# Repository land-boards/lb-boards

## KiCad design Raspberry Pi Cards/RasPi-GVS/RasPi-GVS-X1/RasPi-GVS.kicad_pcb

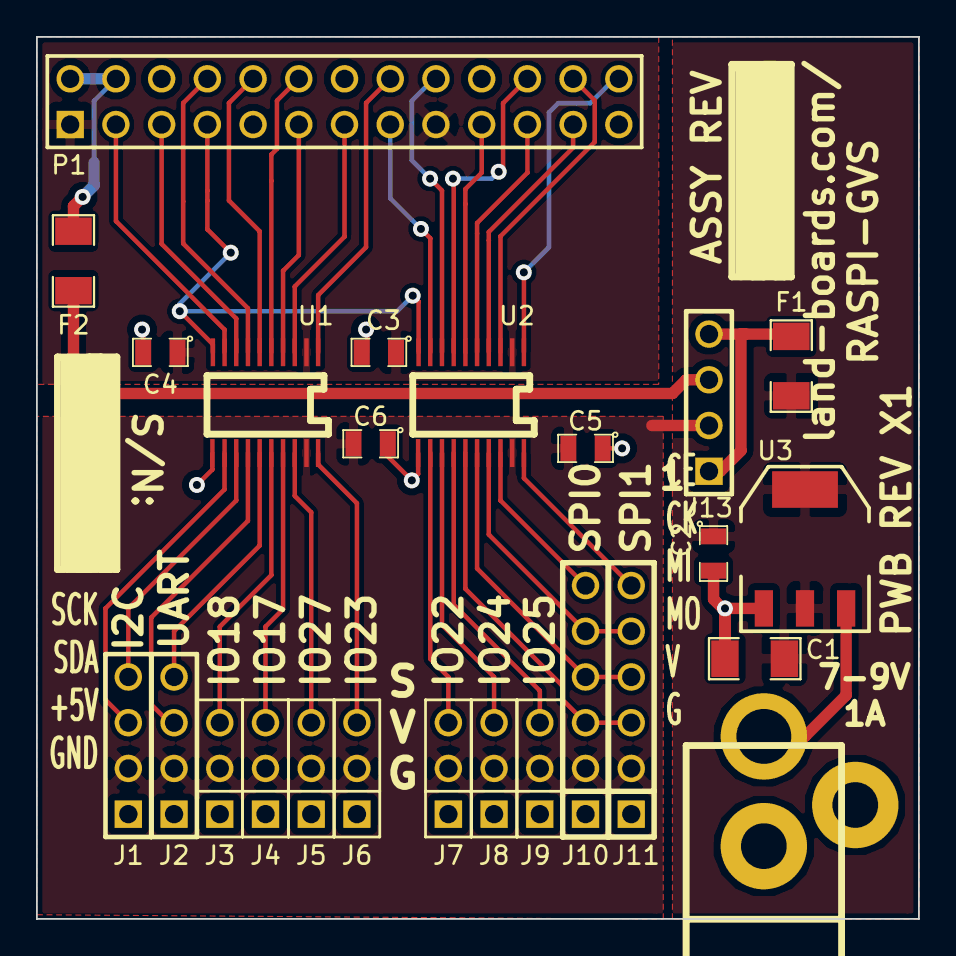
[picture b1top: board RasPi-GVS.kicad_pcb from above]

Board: 2 copper layers, 49.0 x 49.0 mm, 27 parts (0 on the bottom side), 41 nets.

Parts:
C1: 106; SM1206
C2, C3, C4, C5, C6: 104; SM0805
COUP?1, COUP?2: COUPON; REV_BLOCK
F1, F2: FUSE; SM1206
J1, J2, J13: CONN_4; PIN_ARRAY_4x1
J3, J4, J5, J6, J7, J8, J9: CONN_3; PIN_ARRAY_3X1
J10, J11: CONN_6; PIN_ARRAY-6X1
J12: JACK-3.5MM; JACK_2.1MM
P1: RASPIO; pin_array_13x2
U1, U2: TXB0108; SOG20
U3: AP1117; SOT223

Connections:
/+3.3V: C3.1, C4.1, P1.1, P1.17, U1.2, U2.2
/BIO_17: J4.3, U1.17
/BIO_18: J3.3, U1.16
/BIO_22: J7.3, U2.12
/BIO_23: J6.3, U1.20
/BIO_24: J8.3, U2.13
/BIO_25: J9.3, U2.14
/BIO_27: J5.3, U1.18
/BRXD0: J2.4, U1.15
/BSCLK1: J1.4, U1.13
/BSDA1: J1.3, U1.12
/BSPICE0: J10.6, U2.18
/BSPICE1: J11.6, U2.20
/BSPIMISO: J10.4, J11.4, U2.16
/BSPIMOSI: J10.3, J11.3, U2.15
/BSPISCK: J10.5, J11.5, U2.17
/BTXD0: J2.3, U1.14
/GND: C1.2, C2.2, C3.2, C4.2, C5.1, C6.1, J1.1, J2.1, J3.1, J4.1, J5.1, J6.1, J7.1, J8.1, J9.1, J10.1, J11.1, J12.2, J12.3, P1.6, P1.9, P1.14, P1.20, P1.25, U1.11, U2.11, U3.1
/GV5V: C5.2, C6.2, J1.2, J2.2, J3.2, J4.2, J5.2, J6.2, J7.2, J8.2, J9.2, J10.2, J11.2, J13.2, U1.19, U2.19
/IO_4: P1.7, U1.10, U2.10
/IO_17: P1.11, U1.4
/IO_18: P1.12, U1.5
/IO_22: P1.15, U2.9
/IO_23: P1.16, U1.1
/IO_24: P1.18, U2.8
/IO_25: P1.22, U2.7
/IO_27: P1.13, U1.3
/R5: F2.1, P1.2, P1.4
/RP5V: F2.2, J13.3
/RXD0: P1.10, U1.6
/SCLK1: P1.5, U1.8
/SDA1: P1.3, U1.9
/SPICE0: P1.24, U2.3
/SPICE1: P1.26, U2.1
/SPIMISO: P1.21, U2.5
/SPIMOSI: P1.19, U2.6
/SPISCK: P1.23, U2.4
/TXD0: P1.8, U1.7
/VR5V: F1.2, J13.1, J13.4
/VRIN: J12.1, U3.3
/VROUT: C1.1, C2.1, F1.1, U3.2, U3.4

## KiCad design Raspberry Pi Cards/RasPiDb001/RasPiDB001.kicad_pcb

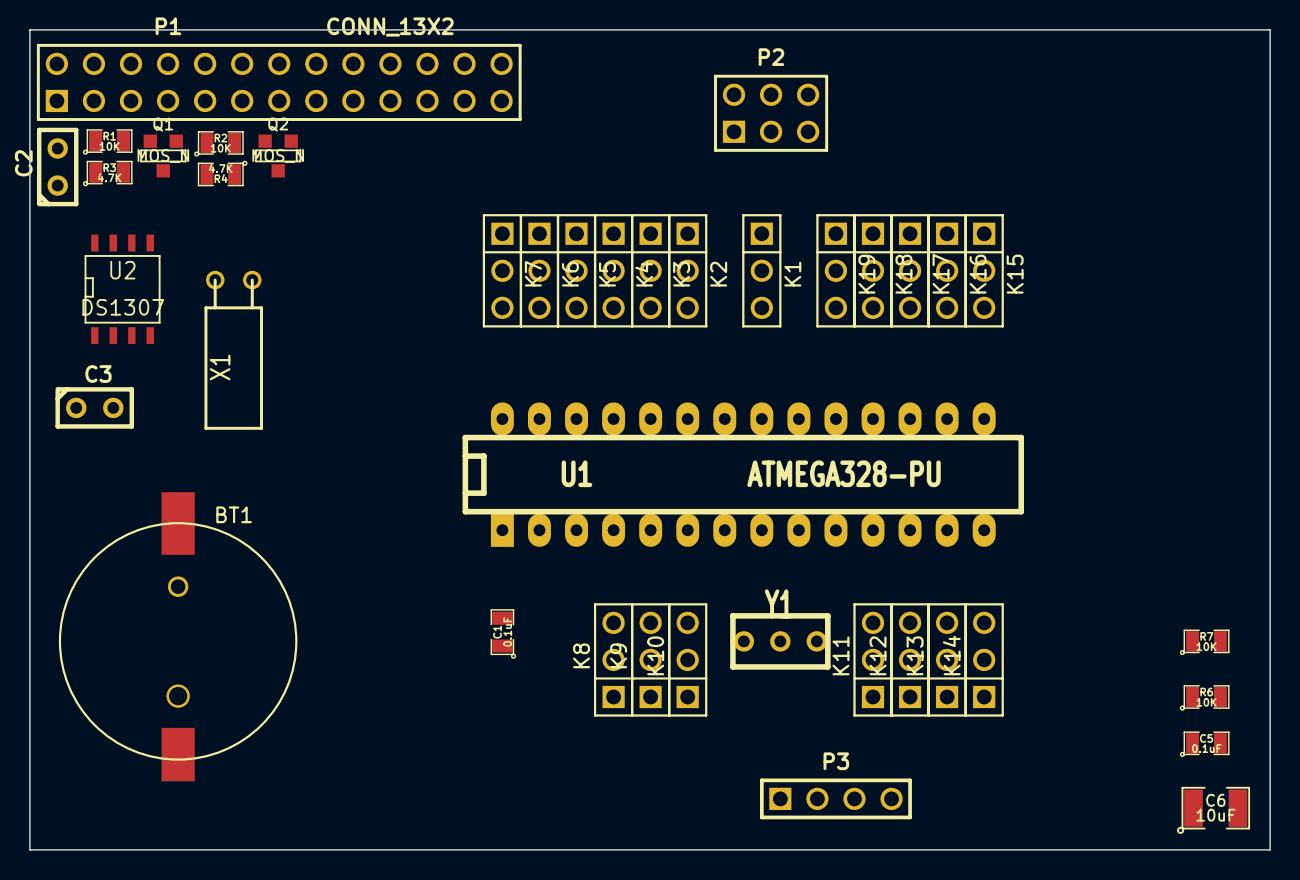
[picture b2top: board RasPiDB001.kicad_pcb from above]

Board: 2 copper layers, 85.0 x 56.2 mm, 40 parts (0 on the bottom side), 35 nets, no tracks yet.

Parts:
BT1: BATTERY; CR1220_CASE
C1, C5: 0.1uF; SM0805
C2, C3: 0.1uF; C1
C6: 10uF; SM1210
K1, K2, K3, K4, K5, K6, K7, K8, K9, K10, K11, K12, K13, K14, K15, K16, K17, K18, K19: CONN_3; PIN_ARRAY_3X1
P1: CONN_13X2; pin_array_13x2
P2: CONN_3X2; pin_array_3x2
P3: CONN_4; PIN_ARRAY_4x1
Q1, Q2: MOS_N; SOT23GDS
R1, R2, R6, R7: 10K; SM0805
R3, R4: 4.7K; SM0805
U1: ATMEGA328-PU; DIP-28__300_ELL
U2: DS1307; SO8N
X1: 32.768KHz; QMONTRE
Y1: 16MHz; RESON_3PIN

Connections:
+3.3V: P1.1, Q1.G, Q2.G, R1.1, R2.1
+5V: C1.1, C3.1, C5.1, C6.1, K1.1, K8.2, K9.2, K10.2, K11.2, K12.2, K13.2, K14.2, K15.2, K16.2, K17.2, K18.2, K19.2, P1.2, P2.2, P3.2, R3.1, R4.2, R6.1, R7.1, U1.7, U1.20, U2.8
/Microprocessor/AD0: K2.3, U1.23
/Microprocessor/AD1: K3.3, U1.24
/Microprocessor/AD2: K4.3, U1.25
/Microprocessor/AD3: K5.3, U1.26
/Microprocessor/AD4: K6.3, U1.27
/Microprocessor/AD5: K7.3, U1.28
/Microprocessor/ARDRX: Q1.D, R3.2, U1.2
/Microprocessor/ARDTX: Q2.D, R4.1, U1.3
/Microprocessor/AREF: K1.3, U1.21
/Microprocessor/D2: K8.3, U1.4
/Microprocessor/D3: K9.3, U1.5
/Microprocessor/D4: K10.3, U1.6
/Microprocessor/D5: K11.3, U1.11
/Microprocessor/D6: K12.3, U1.12
/Microprocessor/D7: K13.3, U1.13
/Microprocessor/D8: K14.3, U1.14
/Microprocessor/D9: K15.3, U1.15
/Microprocessor/D10: K16.3, U1.16
/Microprocessor/D11: K17.3, U1.17
/Microprocessor/D12: K18.3, U1.18
/Microprocessor/D13: K19.3, U1.19
/Microprocessor/RES0: U1.9, Y1.1
/Microprocessor/RES1: U1.10, Y1.3
/RTC/SCLK: P3.4, R6.2, U2.6
/RTC/SDA: P3.3, R7.2, U2.5
/TxRx Transl/PIRX: P1.10, Q2.S, R2.2
/TxRx Transl/PITX: P1.8, Q1.S, R1.2
GND: BT1.2, C1.2, C3.2, C5.2, C6.2, K2.1, K3.1, K4.1, K5.1, K6.1, K7.1, K8.1, K9.1, K10.1, K11.1, K12.1, K13.1, K14.1, K15.1, K16.1, K17.1, K18.1, K19.1, P2.6, P3.1, U1.8, U1.22, U2.4, Y1.2
unnamed: C2.2, U1.1
unnamed: K1.2, K2.2, K3.2, K4.2, K5.2, K6.2, K7.2
unnamed: BT1.1, U2.3
unnamed: U2.1, X1.1
unnamed: U2.2, X1.2

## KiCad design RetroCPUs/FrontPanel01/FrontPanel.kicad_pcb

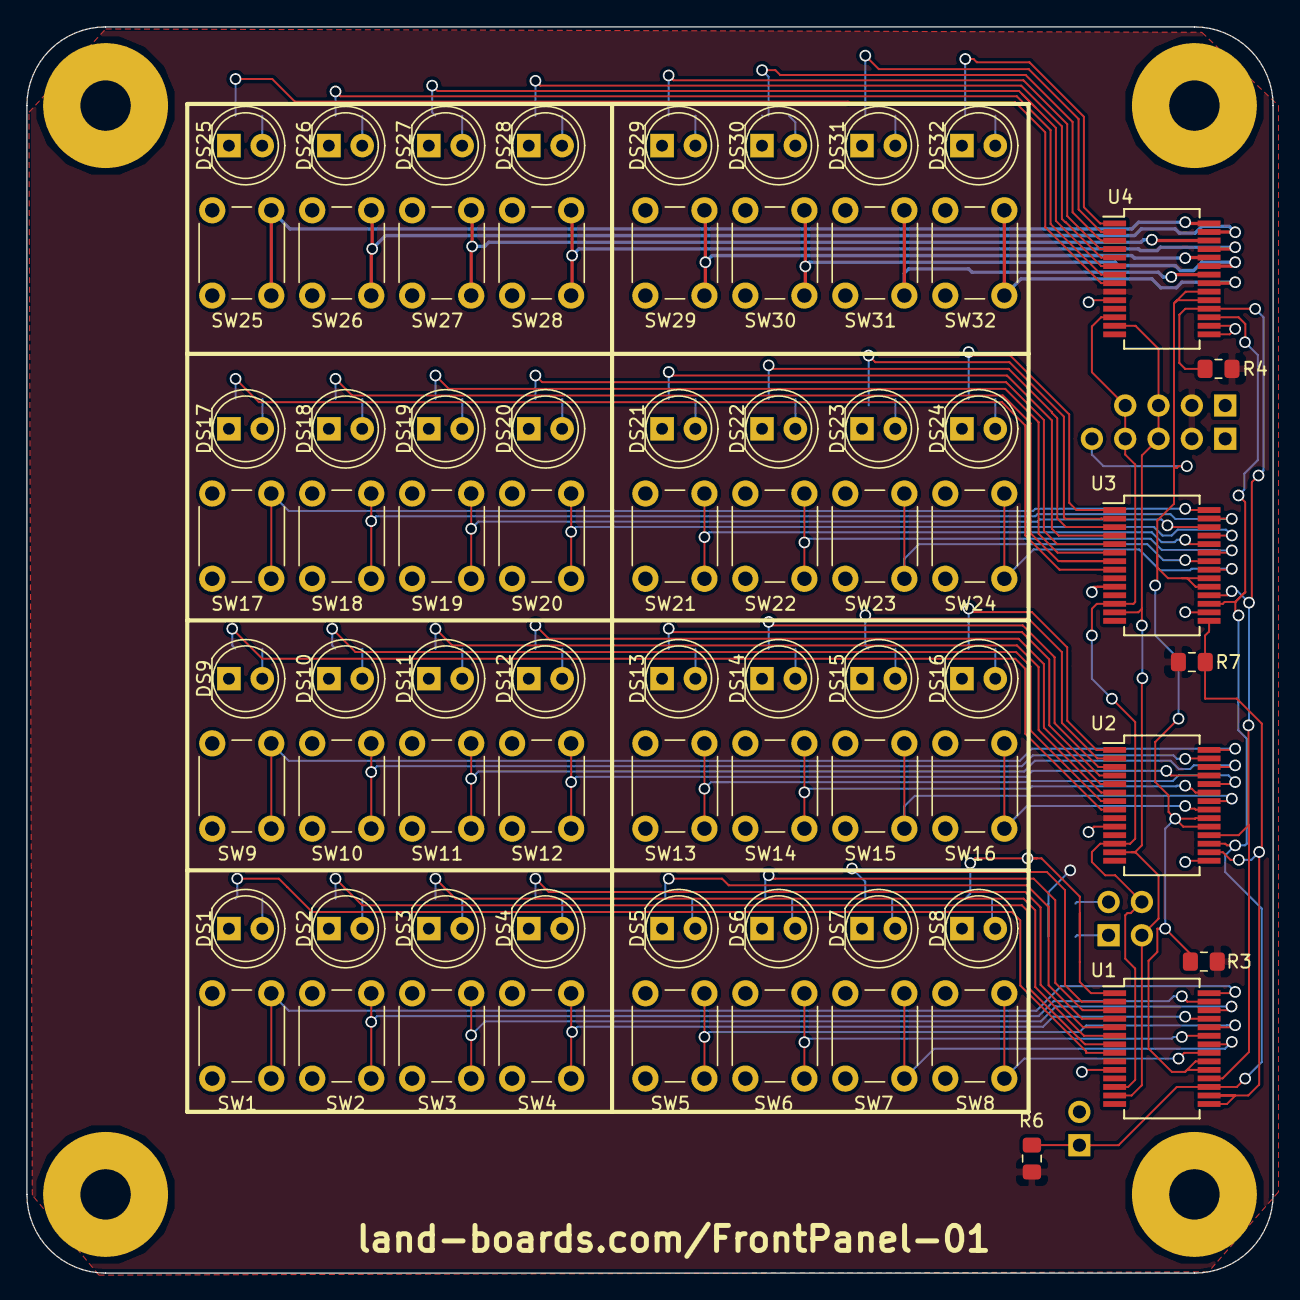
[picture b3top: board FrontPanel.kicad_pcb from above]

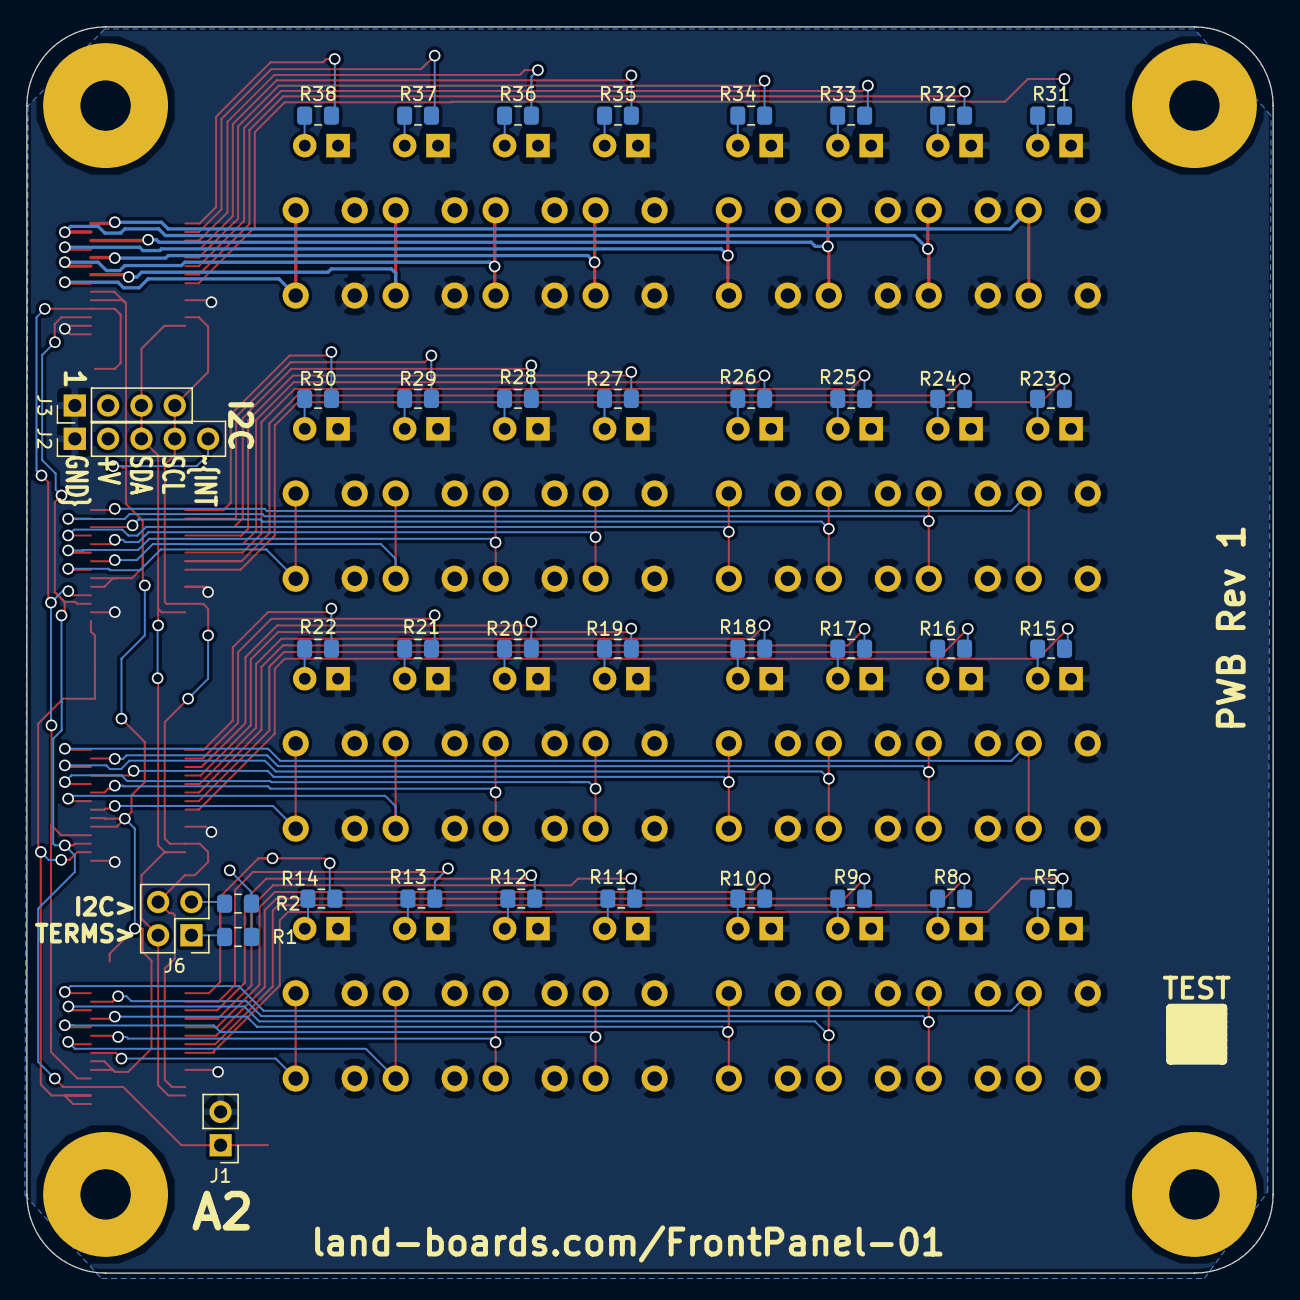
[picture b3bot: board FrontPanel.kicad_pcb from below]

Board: 2 copper layers, 95.0 x 95.0 mm, 115 parts (38 on the bottom side), 106 nets.

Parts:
DS1, DS2, DS3, DS4, DS5, DS6, DS7, DS8, DS9, DS10, DS11, DS12, DS13, DS14, DS15, DS16, DS17, DS18, DS19, DS20, DS21, DS22, DS23, DS24, DS25, DS26, DS27, DS28, DS29, DS30, DS31, DS32: LED; LED_D5.0mm
J1: Conn_01x02; PinHeader_1x02_P2.54mm_Vertical
J2: Conn_01x05; PinHeader_1x05_P2.54mm_Vertical
J3: CONN_4; PinHeader_1x04_P2.54mm_Vertical
J6: CONN_02X02; PinHeader_2x02_P2.54mm_Vertical
MTG1, MTG2, MTG3, MTG4: MTG_HOLE; MTG-6-32
R1, R2: 2.2K; R_0805_2012Metric_Pad1.15x1.40mm_HandSolder
R3, R4, R6, R7: 10K; R_0805_2012Metric_Pad1.15x1.40mm_HandSolder
R5, R8, R9, R10, R11, R12, R13, R14, R15, R16, R17, R18, R19, R20, R21, R22, R23, R24, R25, R26, R27, R28, R29, R30, R31, R32, R33, R34, R35, R36, R37, R38: 330; R_0805_2012Metric_Pad1.15x1.40mm_HandSolder
SW1, SW2, SW3, SW4, SW5, SW6, SW7, SW8, SW9, SW10, SW11, SW12, SW13, SW14, SW15, SW16, SW17, SW18, SW19, SW20, SW21, SW22, SW23, SW24, SW25, SW26, SW27, SW28, SW29, SW30, SW31, SW32: SW_Push; SW_PUSH_6mm
TEST: CONN_1; TEST_BLK-REAR
U1, U2, U3, U4: MCP23017-E/SS; SSOP-28_5.3x10.2mm_P0.65mm

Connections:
+5V: J2.2, J3.2, R1.2, R2.2, R3.1, R4.1, R6.2, R7.1, U1.9, U2.9, U3.9, U4.9
/A2: J1.1, R6.1, U1.17, U2.17, U3.17, U4.17
/PUPADR: R7.2, U1.15, U1.16, U2.16, U3.15
/PUPINT: J2.5, R3.2, U1.19, U1.20, U2.19, U2.20, U3.19, U3.20, U4.19, U4.20
/PUPRST: R4.2, U1.18, U2.18, U3.18, U4.18
/S1D0: SW8.2, U1.21
/S1D1: SW7.2, U1.22
/S1D2: SW6.2, U1.23
/S1D3: SW5.2, U1.24
/S1D4: SW4.2, U1.25
/S1D5: SW3.2, U1.26
/S1D6: SW2.2, U1.27
/S1D7: SW1.2, U1.28
/S2D0: SW16.2, U2.21
/S2D1: SW15.2, U2.22
/S2D2: SW14.2, U2.23
/S2D3: SW13.2, U2.24
/S2D4: SW12.2, U2.25
/S2D5: SW11.2, U2.26
/S2D6: SW10.2, U2.27
/S2D7: SW9.2, U2.28
/S3D0: SW24.2, U3.21
/S3D1: SW23.2, U3.22
/S3D2: SW22.2, U3.23
/S3D3: SW21.2, U3.24
/S3D4: SW20.2, U3.25
/S3D5: SW19.2, U3.26
/S3D6: SW18.2, U3.27
/S3D7: SW17.2, U3.28
/S4D0: SW32.2, U4.21
/S4D1: SW31.2, U4.22
/S4D2: SW30.2, U4.23
/S4D3: SW29.2, U4.24
/S4D4: SW28.2, U4.25
/S4D5: SW27.2, U4.26
/S4D6: SW26.2, U4.27
/S4D7: SW25.2, U4.28
/SCL: J2.4, J3.4, J6.4, U1.12, U2.12, U3.12, U4.12
/SDA: J2.3, J3.3, J6.2, U1.13, U2.13, U3.13, U4.13
GND: DS1.1, DS2.1, DS3.1, DS4.1, DS5.1, DS6.1, DS7.1, DS8.1, DS9.1, DS10.1, DS11.1, DS12.1, DS13.1, DS14.1, DS15.1, DS16.1, DS17.1, DS18.1, DS19.1, DS20.1, DS21.1, DS22.1, DS23.1, DS24.1, DS25.1, DS26.1, DS27.1, DS28.1, DS29.1, DS30.1, DS31.1, DS32.1, J1.2, J2.1, J3.1, SW1.1, SW2.1, SW3.1, SW4.1, SW5.1, SW6.1, SW7.1, SW8.1, SW9.1, SW10.1, SW11.1, SW12.1, SW13.1, SW14.1, SW15.1, SW16.1, SW17.1, SW18.1, SW19.1, SW20.1, SW21.1, SW22.1, SW23.1, SW24.1, SW25.1, SW26.1, SW27.1, SW28.1, SW29.1, SW30.1, SW31.1, SW32.1, U1.10, U2.10, U2.15, U3.10, U3.16, U4.10, U4.15, U4.16
unnamed: DS1.2, R5.1
unnamed: DS2.2, R8.1
unnamed: DS3.2, R9.1
unnamed: DS4.2, R10.1
unnamed: DS5.2, R11.1
unnamed: DS6.2, R12.1
unnamed: DS7.2, R13.1
unnamed: DS8.2, R14.1
unnamed: DS9.2, R15.1
unnamed: DS10.2, R16.1
unnamed: DS11.2, R17.1
unnamed: DS12.2, R18.1
unnamed: DS13.2, R19.1
unnamed: DS14.2, R20.1
unnamed: DS15.2, R21.1
unnamed: DS16.2, R22.1
unnamed: DS17.2, R23.1
unnamed: DS18.2, R24.1
unnamed: DS19.2, R25.1
unnamed: DS20.2, R26.1
unnamed: DS21.2, R27.1
unnamed: DS22.2, R28.1
unnamed: DS23.2, R29.1
unnamed: DS24.2, R30.1
unnamed: DS25.2, R31.1
unnamed: DS26.2, R32.1
unnamed: DS27.2, R33.1
unnamed: DS28.2, R34.1
unnamed: DS29.2, R35.1
unnamed: DS30.2, R36.1
unnamed: DS31.2, R37.1
unnamed: DS32.2, R38.1
unnamed: J6.1, R1.1
unnamed: J6.3, R2.1
unnamed: R5.2, U1.8
unnamed: R8.2, U1.7
unnamed: R9.2, U1.6
unnamed: R10.2, U1.5
unnamed: R11.2, U1.4
unnamed: R12.2, U1.3
unnamed: R13.2, U1.2
unnamed: R14.2, U1.1
unnamed: R15.2, U2.8
unnamed: R16.2, U2.7
unnamed: R17.2, U2.6
unnamed: R18.2, U2.5
unnamed: R19.2, U2.4
unnamed: R20.2, U2.3
unnamed: R21.2, U2.2
unnamed: R22.2, U2.1
unnamed: R23.2, U3.8
unnamed: R24.2, U3.7
unnamed: R25.2, U3.6
unnamed: R26.2, U3.5
unnamed: R27.2, U3.4
unnamed: R28.2, U3.3
unnamed: R29.2, U3.2
unnamed: R30.2, U3.1
unnamed: R31.2, U4.8
unnamed: R32.2, U4.7
unnamed: R33.2, U4.6
unnamed: R34.2, U4.5
unnamed: R35.2, U4.4
unnamed: R36.2, U4.3
unnamed: R37.2, U4.2
unnamed: R38.2, U4.1

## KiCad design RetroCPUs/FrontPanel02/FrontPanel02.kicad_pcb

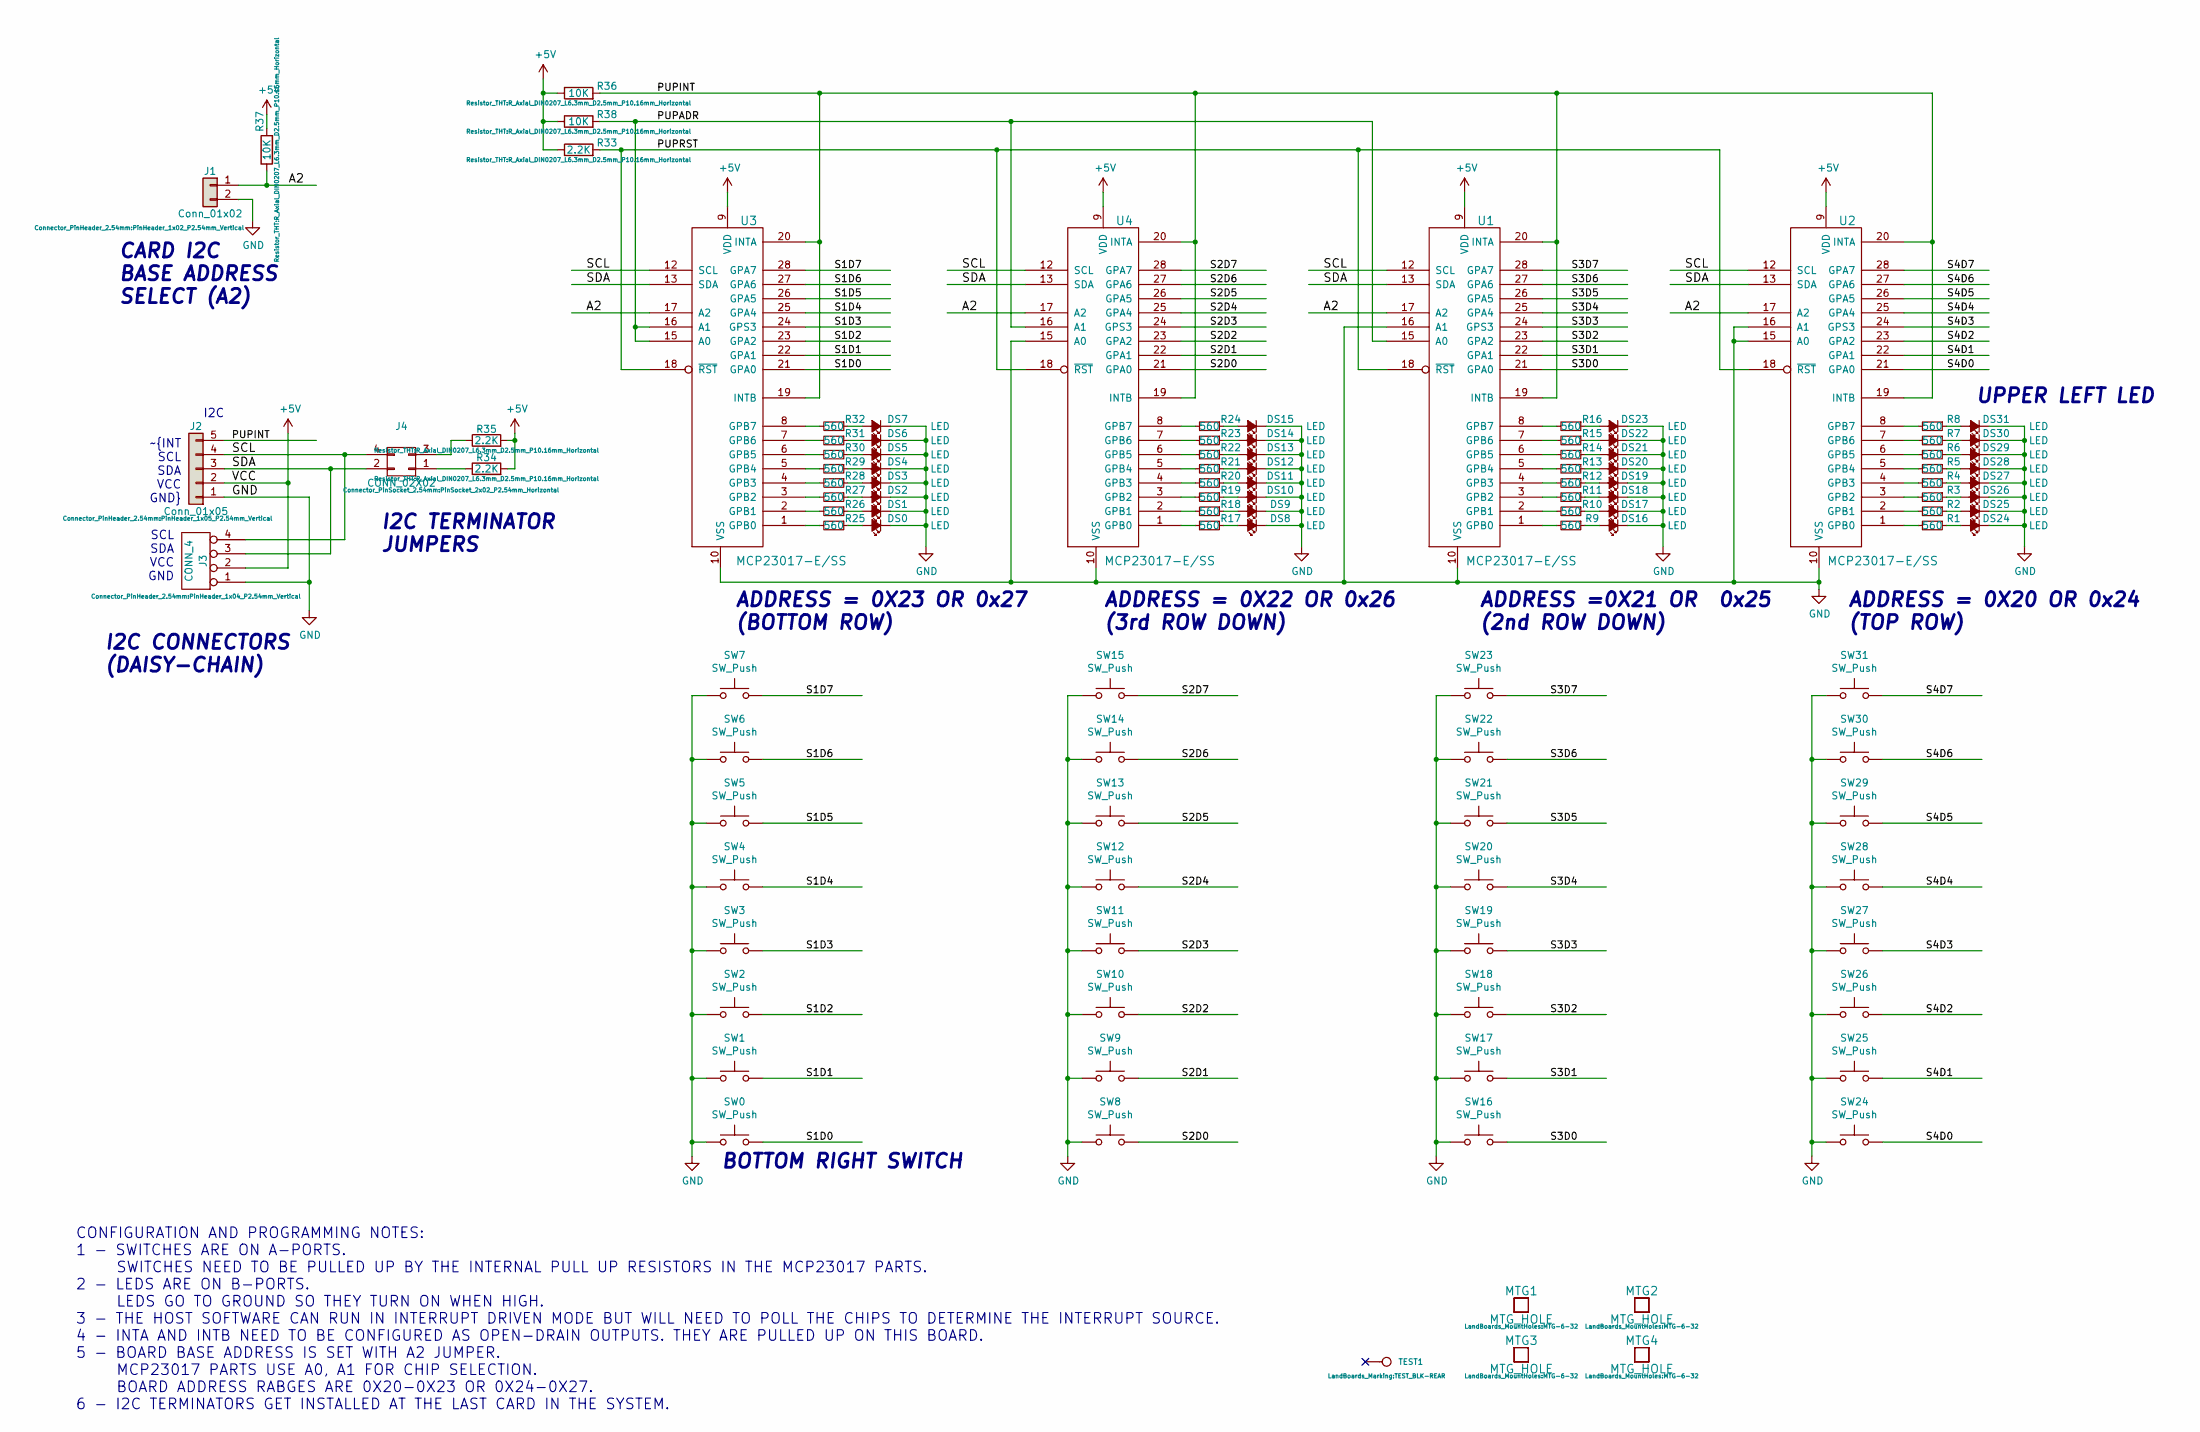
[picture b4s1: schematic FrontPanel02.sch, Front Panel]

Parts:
DS0, DS1, DS2, DS3, DS4, DS5, DS6, DS7, DS8, DS9, DS10, DS11, DS12, DS13, DS14, DS15, DS16, DS17, DS18, DS19, DS20, DS21, DS22, DS23, DS24, DS25, DS26, DS27, DS28, DS29, DS30, DS31: LED; LED_D5.0mm
J1: Conn_01x02; PinHeader_1x02_P2.54mm_Vertical
J2: Conn_01x05; PinHeader_1x05_P2.54mm_Vertical
J3: CONN_4; PinHeader_1x04_P2.54mm_Vertical
J4: CONN_02X02; PinSocket_2x02_P2.54mm_Horizontal
MTG1, MTG2, MTG3, MTG4: MTG_HOLE; MTG-6-32
R1, R2, R3, R4, R5, R6, R7, R8, R9, R10, R11, R12, R13, R14, R15, R16, R17, R18, R19, R20, R21, R22, R23, R24, R25, R26, R27, R28, R29, R30, R31, R32: 560; R_Axial_DIN0207_L6.3mm_D2.5mm_P10.16mm_Horizontal
R33, R34, R35: 2.2K; R_Axial_DIN0207_L6.3mm_D2.5mm_P10.16mm_Horizontal
R36, R37, R38: 10K; R_Axial_DIN0207_L6.3mm_D2.5mm_P10.16mm_Horizontal
SW0, SW1, SW2, SW3, SW4, SW5, SW6, SW7, SW8, SW9, SW10, SW11, SW12, SW13, SW14, SW15, SW16, SW17, SW18, SW19, SW20, SW21, SW22, SW23, SW24, SW25, SW26, SW27, SW28, SW29, SW30, SW31: SW_Push; SW_PUSH_6mm
TEST1: CONN_1; TEST_BLK-REAR
U1, U2, U3, U4: MCP23017-E/SS; DIP-28_W7.62mm_LongPads

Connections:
+5V: J2.2, J3.2, R33.1, R34.2, R35.2, R36.1, R37.2, R38.1, U1.9 (VDD), U2.9 (VDD), U3.9 (VDD), U4.9 (VDD)
/A2: J1.1, R37.1, U1.17 (A2), U2.17 (A2), U3.17 (A2), U4.17 (A2)
/PUPADR: R38.2, U1.15 (A0), U3.15 (A0), U3.16 (A1), U4.16 (A1)
/PUPINT: J2.5, R36.2, U1.19 (INTB), U1.20 (INTA), U2.19 (INTB), U2.20 (INTA), U3.19 (INTB), U3.20 (INTA), U4.19 (INTB), U4.20 (INTA)
/PUPRST: R33.2, U1.18 (~RST), U2.18 (~RST), U3.18 (~RST), U4.18 (~RST)
/S1D0: SW0.2, U3.21 (GPA0)
/S1D1: SW1.2, U3.22 (GPA1)
/S1D2: SW2.2, U3.23 (GPA2)
/S1D3: SW3.2, U3.24 (GPS3)
/S1D4: SW4.2, U3.25 (GPA4)
/S1D5: SW5.2, U3.26 (GPA5)
/S1D6: SW6.2, U3.27 (GPA6)
/S1D7: SW7.2, U3.28 (GPA7)
/S2D0: SW8.2, U4.21 (GPA0)
/S2D1: SW9.2, U4.22 (GPA1)
/S2D2: SW10.2, U4.23 (GPA2)
/S2D3: SW11.2, U4.24 (GPS3)
/S2D4: SW12.2, U4.25 (GPA4)
/S2D5: SW13.2, U4.26 (GPA5)
/S2D6: SW14.2, U4.27 (GPA6)
/S2D7: SW15.2, U4.28 (GPA7)
/S3D0: SW16.2, U1.21 (GPA0)
/S3D1: SW17.2, U1.22 (GPA1)
/S3D2: SW18.2, U1.23 (GPA2)
/S3D3: SW19.2, U1.24 (GPS3)
/S3D4: SW20.2, U1.25 (GPA4)
/S3D5: SW21.2, U1.26 (GPA5)
/S3D6: SW22.2, U1.27 (GPA6)
/S3D7: SW23.2, U1.28 (GPA7)
/S4D0: SW24.2, U2.21 (GPA0)
/S4D1: SW25.2, U2.22 (GPA1)
/S4D2: SW26.2, U2.23 (GPA2)
/S4D3: SW27.2, U2.24 (GPS3)
/S4D4: SW28.2, U2.25 (GPA4)
/S4D5: SW29.2, U2.26 (GPA5)
/S4D6: SW30.2, U2.27 (GPA6)
/S4D7: SW31.2, U2.28 (GPA7)
/SCL: J2.4, J3.4, J4.4, U1.12 (SCL), U2.12 (SCL), U3.12 (SCL), U4.12 (SCL)
/SDA: J2.3, J3.3, J4.2, U1.13 (SDA), U2.13 (SDA), U3.13 (SDA), U4.13 (SDA)
GND: DS0.1 (K), DS1.1 (K), DS2.1 (K), DS3.1 (K), DS4.1 (K), DS5.1 (K), DS6.1 (K), DS7.1 (K), DS8.1 (K), DS9.1 (K), DS10.1 (K), DS11.1 (K), DS12.1 (K), DS13.1 (K), DS14.1 (K), DS15.1 (K), DS16.1 (K), DS17.1 (K), DS18.1 (K), DS19.1 (K), DS20.1 (K), DS21.1 (K), DS22.1 (K), DS23.1 (K), DS24.1 (K), DS25.1 (K), DS26.1 (K), DS27.1 (K), DS28.1 (K), DS29.1 (K), DS30.1 (K), DS31.1 (K), J1.2, J2.1, J3.1, SW0.1, SW1.1, SW2.1, SW3.1, SW4.1, SW5.1, SW6.1, SW7.1, SW8.1, SW9.1, SW10.1, SW11.1, SW12.1, SW13.1, SW14.1, SW15.1, SW16.1, SW17.1, SW18.1, SW19.1, SW20.1, SW21.1, SW22.1, SW23.1, SW24.1, SW25.1, SW26.1, SW27.1, SW28.1, SW29.1, SW30.1, SW31.1, U1.10 (VSS), U1.16 (A1), U2.10 (VSS), U2.15 (A0), U2.16 (A1), U3.10 (VSS), U4.10 (VSS), U4.15 (A0)
unnamed: DS0.2 (A), R25.1
unnamed: DS1.2 (A), R26.1
unnamed: DS2.2 (A), R27.1
unnamed: DS3.2 (A), R28.1
unnamed: DS4.2 (A), R29.1
unnamed: DS5.2 (A), R30.1
unnamed: DS6.2 (A), R31.1
unnamed: DS7.2 (A), R32.1
unnamed: DS8.2 (A), R17.1
unnamed: DS9.2 (A), R18.1
unnamed: DS10.2 (A), R19.1
unnamed: DS11.2 (A), R20.1
unnamed: DS12.2 (A), R21.1
unnamed: DS13.2 (A), R22.1
unnamed: DS14.2 (A), R23.1
unnamed: DS15.2 (A), R24.1
unnamed: DS16.2 (A), R9.1
unnamed: DS17.2 (A), R10.1
unnamed: DS18.2 (A), R11.1
unnamed: DS19.2 (A), R12.1
unnamed: DS20.2 (A), R13.1
unnamed: DS21.2 (A), R14.1
unnamed: DS22.2 (A), R15.1
unnamed: DS23.2 (A), R16.1
unnamed: DS24.2 (A), R1.1
unnamed: DS25.2 (A), R2.1
unnamed: DS26.2 (A), R3.1
unnamed: DS27.2 (A), R4.1
unnamed: DS28.2 (A), R5.1
unnamed: DS29.2 (A), R6.1
unnamed: DS30.2 (A), R7.1
unnamed: DS31.2 (A), R8.1
unnamed: J4.1, R34.1
unnamed: J4.3, R35.1
unnamed: R1.2, U2.1 (GPB0)
unnamed: R2.2, U2.2 (GPB1)
unnamed: R3.2, U2.3 (GPB2)
unnamed: R4.2, U2.4 (GPB3)
unnamed: R5.2, U2.5 (GPB4)
unnamed: R6.2, U2.6 (GPB5)
unnamed: R7.2, U2.7 (GPB6)
unnamed: R8.2, U2.8 (GPB7)
unnamed: R9.2, U1.1 (GPB0)
unnamed: R10.2, U1.2 (GPB1)
unnamed: R11.2, U1.3 (GPB2)
unnamed: R12.2, U1.4 (GPB3)
unnamed: R13.2, U1.5 (GPB4)
unnamed: R14.2, U1.6 (GPB5)
unnamed: R15.2, U1.7 (GPB6)
unnamed: R16.2, U1.8 (GPB7)
unnamed: R17.2, U4.1 (GPB0)
unnamed: R18.2, U4.2 (GPB1)
unnamed: R19.2, U4.3 (GPB2)
unnamed: R20.2, U4.4 (GPB3)
unnamed: R21.2, U4.5 (GPB4)
unnamed: R22.2, U4.6 (GPB5)
unnamed: R23.2, U4.7 (GPB6)
unnamed: R24.2, U4.8 (GPB7)
unnamed: R25.2, U3.1 (GPB0)
unnamed: R26.2, U3.2 (GPB1)
unnamed: R27.2, U3.3 (GPB2)
unnamed: R28.2, U3.4 (GPB3)
unnamed: R29.2, U3.5 (GPB4)
unnamed: R30.2, U3.6 (GPB5)
unnamed: R31.2, U3.7 (GPB6)
unnamed: R32.2, U3.8 (GPB7)

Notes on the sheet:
SCL SDA VCC GND
~INT SCL SDA VCC GND
I2C
CARD I2C BASE ADDRESS SELECT (A2)
I2C TERMINATOR JUMPERS
I2C CONNECTORS (DAISY-CHAIN)
CONFIGURATION AND PROGRAMMING NOTES: 1 - SWITCHES ARE ON A-PORTS. SWITCHES NEED TO BE PULLED UP BY THE INTERNAL PULL UP RESISTORS IN THE MCP23017 PARTS. 2 - LEDS ARE ON B-PORTS. LEDS GO TO GROUND SO THEY TURN ON WHEN HIGH. 3 - THE HOST SOFTWARE CAN RUN IN INTERRUPT DRIVEN MODE BUT WILL NEED TO POLL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
ADDRESS =0X21 OR 0x25 (2nd ROW DOWN)
ADDRESS = 0X22 OR 0x26 (3rd ROW DOWN)
ADDRESS = 0X23 OR 0x27 (BOTTOM ROW)
ADDRESS = 0X20 OR 0x24 (TOP ROW)
BOTTOM RIGHT SWITCH
UPPER LEFT LED

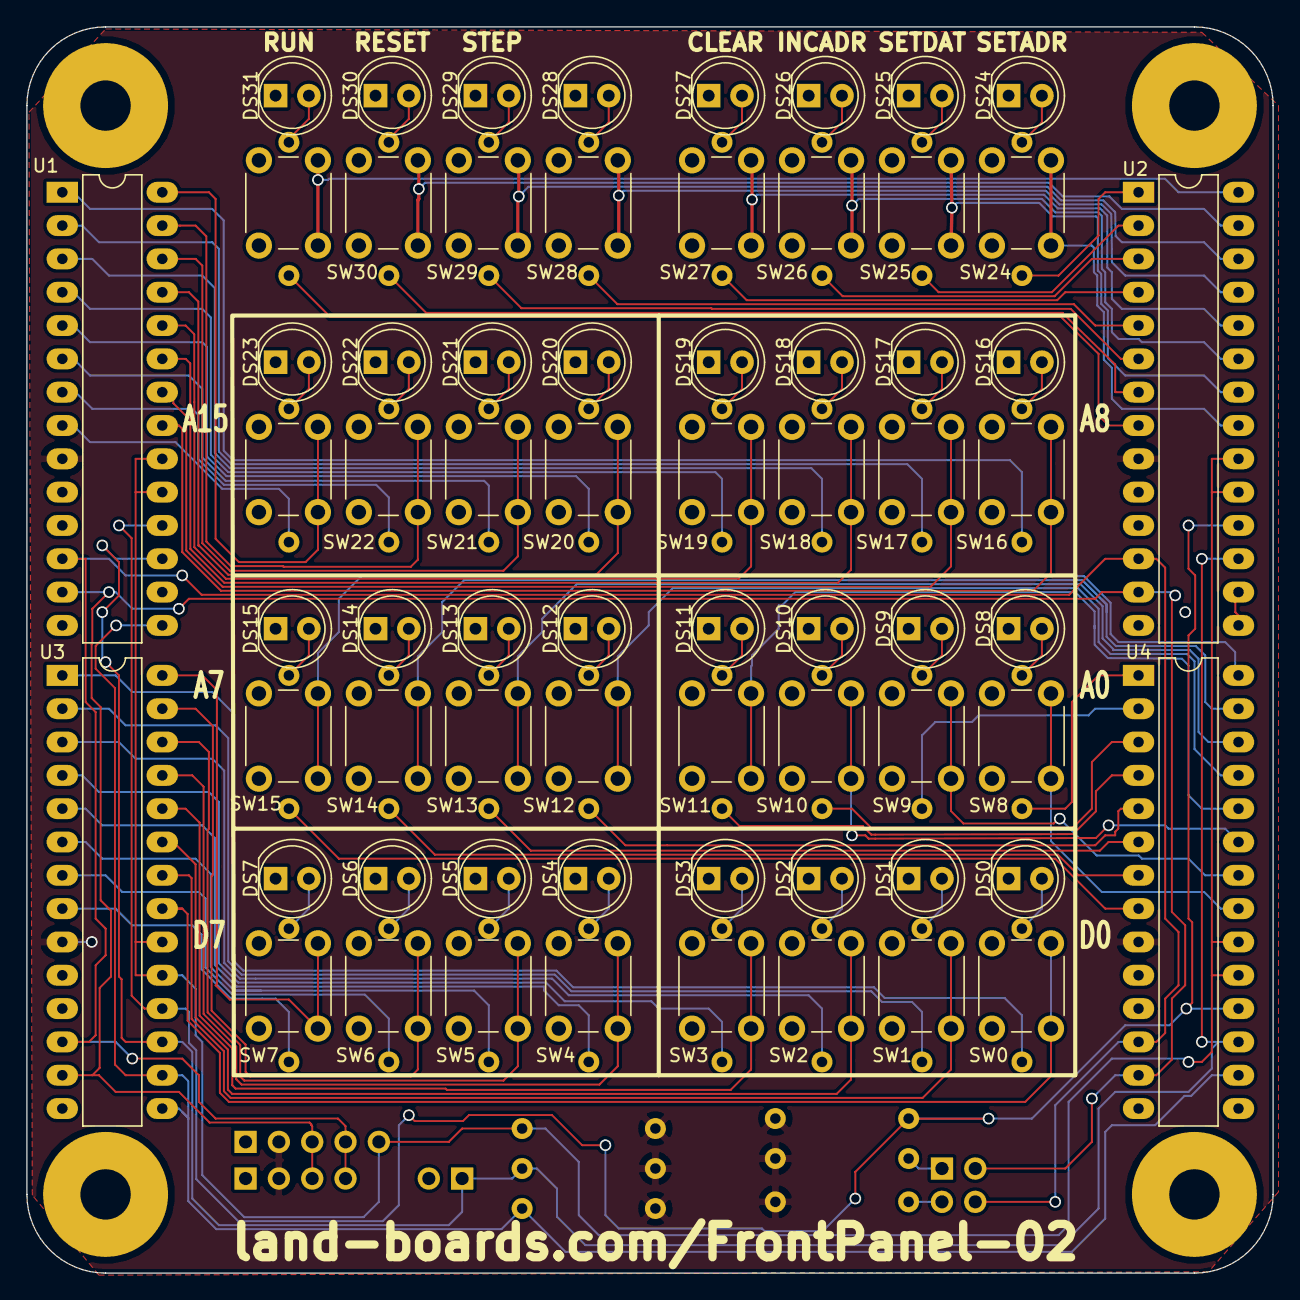
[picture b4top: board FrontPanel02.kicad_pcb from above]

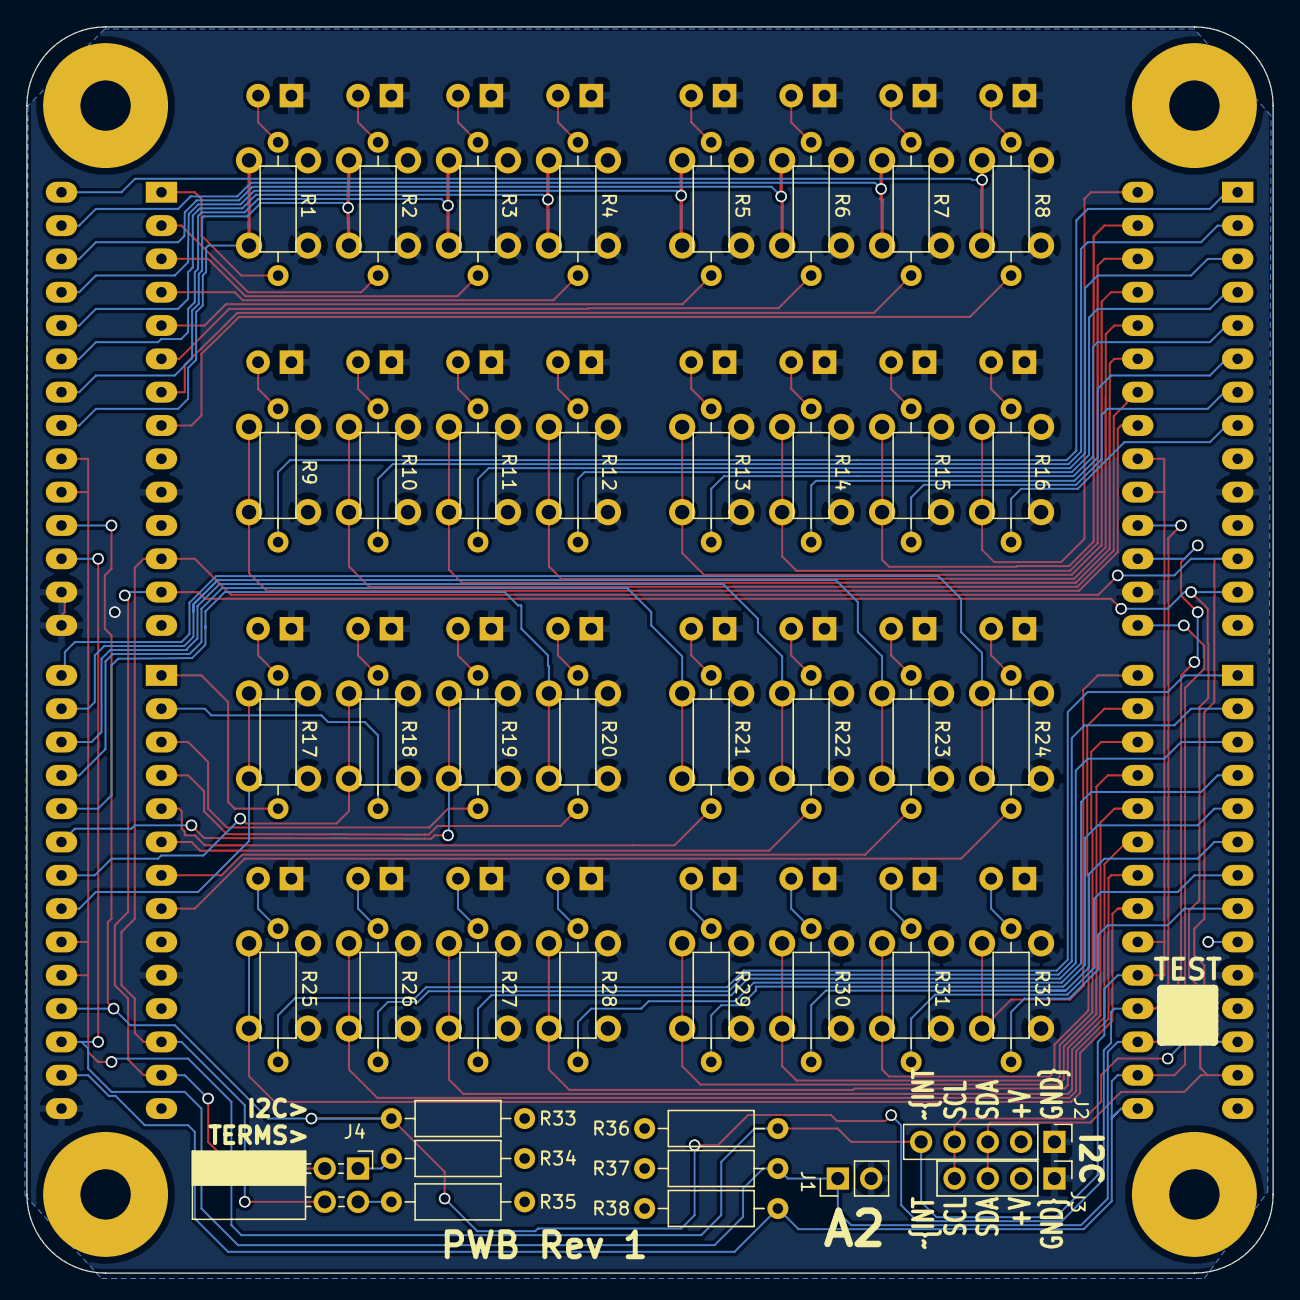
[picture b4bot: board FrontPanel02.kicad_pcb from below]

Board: 2 copper layers, 95.0 x 95.0 mm, 115 parts (42 on the bottom side), 106 nets.

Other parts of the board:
TEST: CONN_1; TEST_BLK-REAR

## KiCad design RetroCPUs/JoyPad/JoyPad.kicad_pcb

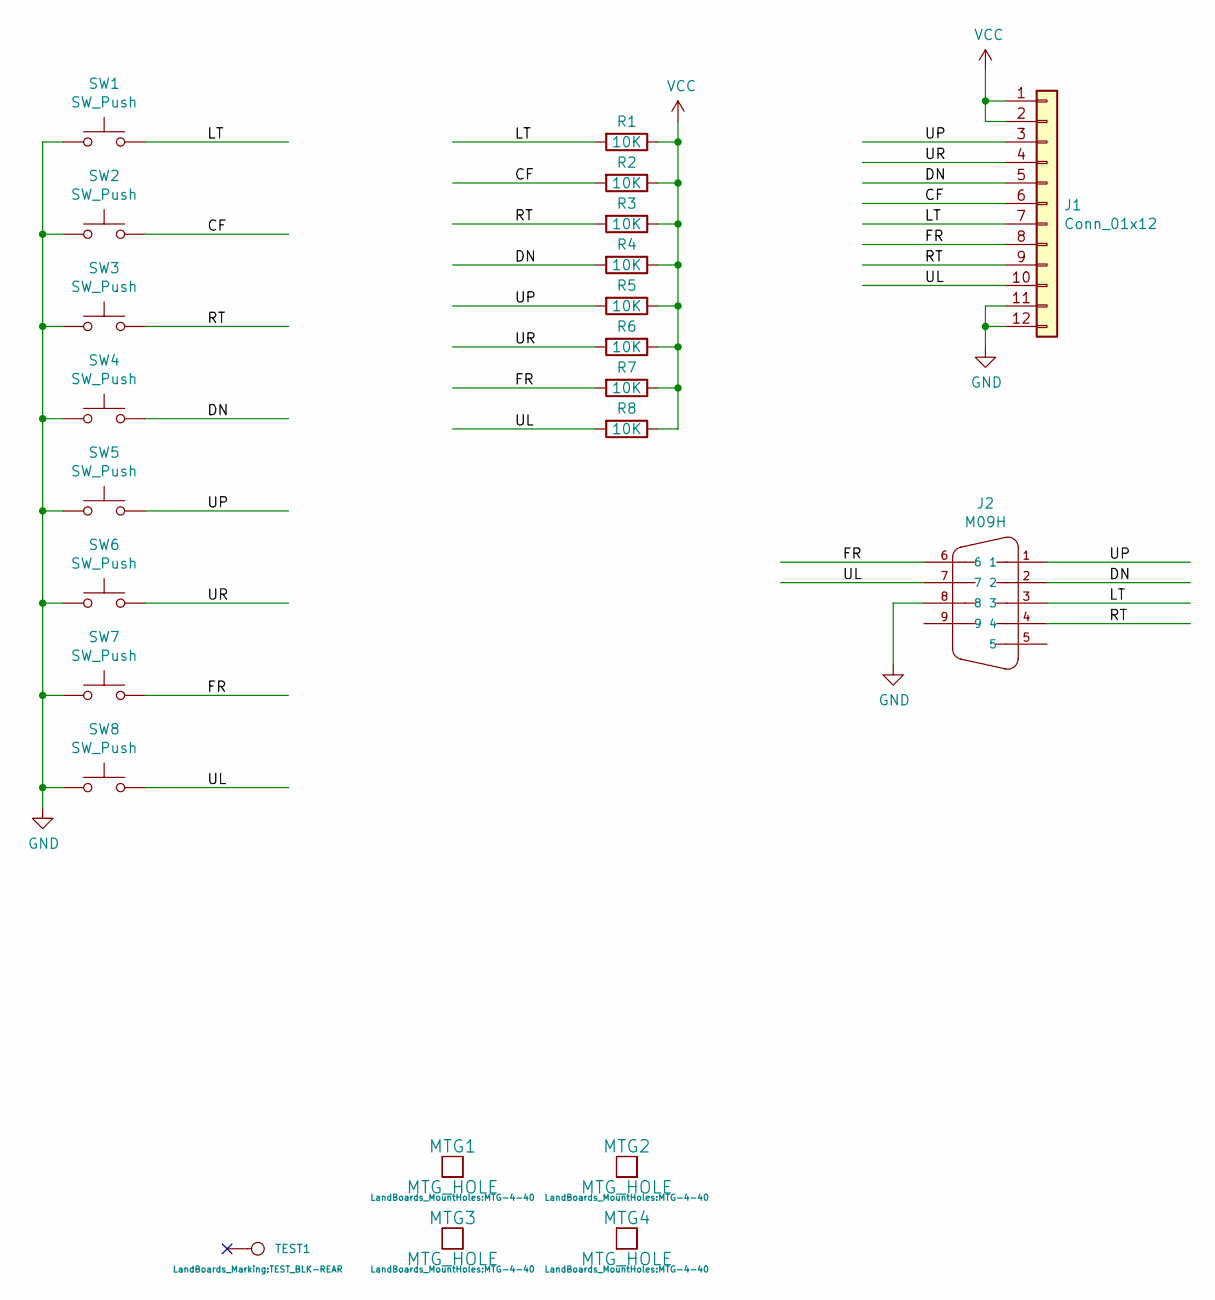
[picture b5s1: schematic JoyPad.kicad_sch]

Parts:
J1: Conn_01x12; PinHeader_1x12_P2.54mm_Vertical
J2: M09H; DSUB-9_Female_Horizontal_P2.77x2.84mm_EdgePinOffset4.94mm_H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
MTG1, MTG2, MTG3, MTG4: MTG_HOLE; MTG-4-40
R1, R2, R3, R4, R5, R6, R7, R8: 10K; R_0805_2012Metric_Pad1.15x1.40mm_HandSolder
SW1, SW2, SW3, SW4, SW5, SW6, SW7, SW8: SW_Push; SW_PUSH_6mm
TEST1: CONN_1; TEST_BLK-REAR

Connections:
/CF: J1.6, R2.2, SW2.2
/DN: J1.5, J2.2, R4.2, SW4.2
/FR: J1.8, J2.6, R7.2, SW7.2
/LT: J1.7, J2.3, R1.2, SW1.2
/RT: J1.9, J2.4, R3.2, SW3.2
/UL: J1.10, J2.7, R8.2, SW8.2
/UP: J1.3, J2.1, R5.2, SW5.2
/UR: J1.4, R6.2, SW6.2
GND: J1.11, J1.12, J2.8, SW1.1, SW2.1, SW3.1, SW4.1, SW5.1, SW6.1, SW7.1, SW8.1
VCC: J1.1, J1.2, R1.1, R2.1, R3.1, R4.1, R5.1, R6.1, R7.1, R8.1
